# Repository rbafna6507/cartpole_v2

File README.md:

# Cartpole v2

Start here: [complete system README](SYSTEM_README.md), [command cheat sheet](COMMAND_CHEATSHEET.md), [all CLI arguments](COMMAND_REFERENCE.md), [source/evidence index](SYSTEM_REFERENCE.md), and [preservation audit](PRESERVATION_AUDIT_20261023.md).

October 26 offline developer update: [start with one controller in simulation, replay and submission](docs/CONTROLLER_DEVELOPER_GUIDE.md), use the [agent-facing portal API](docs/portal.md), and [export run bundles for analysis](docs/RUN_RECORDING.md). These source changes share the pinned `rig-calibrated-20261021-v1` development profile; deploying them and accepting full-duration physical runs remain separate work. Native/Python AUTO are hand-designed controllers, not separately trained policies; see the [offline comparison](docs/python-auto-offline-audit-20261026.md).

October 23 operator release: on the Jetson, `cd ~/cartpole-v2-live/active && uv run cartpole`, or use `cartpole-console` from PATH. In the console, load `policies/working.json` (user-tested 102,400 steps) or `policies/1m.json` (1,024,000-step candidate), then use `policy check swingup` and explicit `policy swingup 25` from a settled, homed hanging start. Deployment itself performs no motion.

For the vertical-enabled runtime, use the deployment copies `policies/working.json` and `policies/1m.json`. Their weights, experiment identities, and observation/action contracts are unchanged; only the reviewed runtime pins and enclosing content digest were migrated. [Migration evidence](policies/vertical-runtime-migration.json) records the original and deployed hashes plus exact numeric inference parity. Original `training/candidates/.../actor.json` files remain immutable and pinned to their archived runtime; the strict loader intentionally refuses them under changed runtime sources. This migration does not confer hardware acceptance.

Locally, `uv run --locked --extra sim cartpole-view-policy` opens the learned Gym viewer; add `--controller reference` for the saved traditional gains on the fitted plant, or `--actor policies/1m.json` for the new candidate. See the cheat sheet for all training, evaluation, console and deployment options.

The sections below retain earlier subsystem introductions. Dated historical measurements: [2026-10-20 checkpoint](docs/checkpoint-20261020.md).

The SDK now connects to a new Teensy safety executor, runs the preserved controller
on hardware, and supports Python policies, MuJoCo simulation, policy training,
recordings, source-specific sensing, and an isolated submission queue. The working
controller and vision3 remain unchanged in `archive/`.

The real SDK/Teensy path completed a ten-second swing-up/balance trial and a slow
return to center. USB telemetry delivered up to 1,000 Hz in stopped tests; a
250 Hz zero-command loop and action expiry were also verified. This does not
establish hard real-time host control or hardware acceptance of learned policies.

## Collect the remaining system identification data

Use `./scripts/system-id-campaign` for repeatable cart-response/timing/AUTO
campaigns and guided motor-disabled angular/cart measurements. Start with
`./scripts/system-id-campaign plan`; an offline `rehearse` command exercises the
artifact/review workflow without hardware. See [collection commands, review,
and portable evidence bundles](docs/system-id-campaign.md). Collection does not
change the existing simulation or trained policy profiles.

## Open the interactive demo

```bash
uv run --locked --extra sim cartpole-v2-view
```

Space pauses, R resets, and Esc exits. The command selects `mjpython` on macOS.
The initial overlay deadlock is fixed and native rendering/pause/reset have been
verified. Episodes intentionally freeze at 30 simulated seconds until R.
See [viewer controls and verification](docs/viewer.md).

## Use the new firmware and SDK

With the executor already installed, inspect the stopped board on the Jetson:

```bash
uv run --locked --extra hardware cartpole-console \
  --port /dev/serial/by-id/usb-Teensyduino_USB_Serial_20242870-if00 --command info
```

The console also provides `auto`, `bal`, external policies, homing, and explicit
switchless commissioning. Read [rig usage](docs/rig-usage.md) before motion and
[executor protocol and programming](docs/executor.md) before uploading firmware.
**Motor power must be off during every flash, bootloader entry, or board reset.**
The existing PCB does not hold the shared enable input disabled without firmware;
clicking was observed during programming and the board was recovered with motor
power off. A hardware default-disable circuit remains necessary.

[PCB switch wiring](docs/pcb-switches.md) specifies normally-closed contacts.
Switch 1 is the left cart limit and switch 2 the right. Physical two-end homing
measured 619.2 mm of travel; `rehome` returns to the established center. Only these
two switches are required for cart motion. Uninstalled D28/D29 remain diagnostic
inputs, Z pulses are disabled, and every boot enables the cart switch interlock.
See [current commands and commissioning evidence](docs/rig-usage.md).

The current operator release is `platform-20261015-v6-tunable`, running
`executor-v6-measuredrail`. The console loads the preserved bandwidth-10 gains
by default (`pw=3`, jerk 150 m/s³). Repeated native AUTO trials captured in about
2.5 seconds; two 60-second trials held continuously for about 57.5 seconds after
capture. A separate bandwidth-8 smoothing candidate also completed a 60-second
trial with return. These are measured bounded results, not unlimited stability.
The working encoder reference is 330 counts, an experimental constant trim;
there is still no accepted hanging-only or nonlinear calibration model.

See the [October 16 checkpoint](docs/checkpoint-20261016.md),
[tuning and jitter evidence](evidence/phase3/jitter-20261016/README.txt), and
[preserved Jetson releases](releases/README.md). The experimental Python AUTO/BAL implementation now runs through the SDK on the
physical rig. One 25-second Python AUTO trial captured at 3.17 seconds and held
for the remaining 21.8 seconds; other trials exposed host timing and an early
right-switch stop. It is not yet a repeatably commissioned replacement for native
control. See [Python control, gain explanations and identification](docs/python-control-20261016.md).
Release snapshots preserve the established native operator software separately.

## Persistent vision and SDK sensing

The maintained camera runtime is `src/cartpole_vision`; `archive/vision3` stays
unchanged. The Jetson's `cartpole-vision.service` keeps the camera portal running
independently of the console. From a computer on the same Tailscale network:

```sh
python3 scripts/vision-view.py --host 100.126.59.18 --port 13090
```

Open **http://127.0.0.1:13090/**. The portal provides camera, tracked overlay, green
mask, measured rates and plots. The v2 console automatically publishes its
accepted encoder telemetry; closing it marks encoder readings stale while the
camera continues. The camera service never opens serial. An isolated vision
environment prevents normal console installs from removing its dependencies.

[Vision setup and measured performance](docs/vision-usage.md) describes the private
viewer, SSH fallback, service and camera configuration. [SDK sensing](docs/sensing.md)
describes explicit frames and timestamps, the actual shadow fusion monitor, and
hanging model validation. Shadow fusion was verified against stopped live data;
it remains uncommissioned and does not control motion.

## Policies, identification and the portal

- [Host-rate Python control and reproducible RL](docs/policies.md): separate
  100/250 Hz controllers, raw-demand executor simulation, training and held-out
  evaluation. The learned artifact is numeric JSON; hardware transfer is unproven.
- [Model-bound PPO and Colab training](docs/rl-training.md): neural training,
  checkpoint resume, disjoint evaluation and a portable SDK actor using the
  governed/observed simulator. Current model scopes remain development only;
  physical model and learned-policy acceptance are separate gates.
- [Sensing and physical identification](docs/identification.md): explicit clocks,
  calibration, validity and held-out rejection. The MuJoCo plant remains provisional.
- [Runnable system-identification workflow](docs/system-identification-workflow.md):
  labelled release protocols, raw-data and frozen-fit plots, independent validation,
  scoped model export and Gym loading. [PPO and Colab](docs/rl-training.md) adds
  neural training, resumable checkpoints and a portable SDK actor using the
  governed, encoder-observed `RigCartpoleEnv`. Physical-model acceptance remains
  separate from software readiness.
  [October 17 measurements and plots](evidence/system-id-20261017/README.md) record
  the latest physical results; model acceptance for hardware RL remains open.
- [Portal and isolated worker](docs/portal.md): authenticated immutable uploads,
  durable single-rig queue, results and a Linux sandbox. The service defaults to
  loopback. Public hosting and learned-policy hardware acceptance remain deployment gates.
- [Current implementation and acceptance state](docs/platform-status.md).
- [Detailed execution plan](docs/live-rig-plan.md).

## Try the controller in simulation

```bash
mkdir -p runs/demo
uv run --locked --extra sim cartpole-v2 simulate runs/demo/swingup --steps 10000
uv run --locked --extra sim cartpole-v2 simulate runs/demo/upright --start upright --steps 10000
uv run --locked --extra sim python examples/gym_rollout.py --steps 200 --seed 7
```

The first two commands save observations, action/plant traces, model and parameters
in new directories. The model uses provisional physical parameters; successful
simulation does not establish hardware transfer. See [Phase 2 usage](docs/phase2-usage.md)
for custom Python policies, Gymnasium, sensor timing, model configuration and limits.

## Try the Python SDK locally

```bash
mkdir -p runs/sdk-demo
uv run --locked cartpole-v2 import-vision tests/fixtures/vision-real.jsonl runs/sdk-demo/vision.jsonl --session-id demo-vision --frame-id vision:demo-calibration
uv run --locked cartpole-v2 inspect runs/sdk-demo/vision.jsonl
uv run --locked python examples/replay_policy.py runs/sdk-demo/vision.jsonl runs/sdk-demo/my-policy.jsonl --frame-id vision:demo-calibration
```

Edit `MyPolicy` in `examples/replay_policy.py` to experiment. The example receives
real recorded vision observations and writes acceleration requests to a local
trace. Replay uses fixed inputs; it does not simulate the resulting rig motion.
The example is an illustrative mapping, not the tuned balancing controller.
Outputs are never overwritten; choose fresh paths when repeating commands.

See [SDK usage, data semantics and next integrations](docs/phase1-usage.md).
Run maintained tests with
`uv run --locked --extra sim --extra hardware --extra vision --group dev python -m pytest`
(C++17 compiler required for native firmware tests). Archived projects retain
their own separate environments and test commands.

## Run the baseline

The archived console requires the original v33 firmware. The currently installed
executor uses the new console above; the two wire protocols are different. Restore
an archived firmware only with motor power off. With v33 installed, run from the
repository root on the Jetson:

```bash
uv run --project archive/good_balancing_jetson cartpole-console --rate 100
```

The console restores the saved tuning while stopped, verifies 33 parameters and
8 computed gains, and opens the terminal interface. It does not start motion or
restore an old home/upright reference. Close any other Teensy console first.

To use the preserved camera baseline instead of the maintained service, first stop
`cartpole-vision.service`, then run in a separate Jetson terminal with no other
camera owner:

```bash
cd archive/vision3
uv run vision3 --camera /dev/video0 --calibration-file last_calibration.json
```

On the Mac, from the repository root:

```bash
./archive/vision-tunnel.sh
```

After SSH connects, open **http://127.0.0.1:3095/**. Keep the tunnel terminal open.
The tunnel discovers the current direct IPv6 address through a read-only query
using `ssh rbafna@jetson`, then verifies reachability and reuses the trusted host identity.
It needs a working bootstrap SSH key/agent; the final connection can still ask for
your normal password. To preview the selection, use
`./archive/vision-tunnel.sh --print-command`. An explicit destination bypasses
discovery: `./archive/vision-tunnel.sh rbafna@jetson` uses the configured route.
It does not start the camera or control the rig.

- [Jetson setup and testing](docs/jetson-testing.md)
- [Archive contents and recovery](archive/README.md)
- [Console, gains, and firmware](archive/good_balancing_jetson/README.md)
- [Vision, calibration, and system dependencies](archive/vision3/README.md)
- [Control rates, languages, and transport choice](docs/control-timing-and-transport.md)
- [Revised v2 architecture](docs/architecture.md)
- [Phase 2 implementation plan](docs/phase2-plan.md)
- [Phase 2 verification](evidence/phase2/verification.json)
- [Phase 1 implementation plan](docs/phase1-plan.md)
- [Phase 0 plan and decisions](docs/phase0-plan.md)
- [Phase 1 verification](evidence/phase1/verification.json)
- [Phase 0 verification](evidence/phase0/verification.json)

Both projects pin Python 3.11 for `uv` and include a universal `uv.lock`. Their
commands are intended to run from an editable repository checkout; this archive
is not a standalone wheel distribution. Do not copy `.venv` between computers.

No Jetson access, camera capture, firmware upload, or physical motion was performed
during Phase 0. New control and vision work uses directories outside the preserved archived
baselines; later physical work is recorded under `evidence/phase3` and `phase4`.

Controller authors: [SDK data and development guide](docs/CONTROLLER_DEVELOPER_GUIDE.md). The portal now requires operator approval for each physical job; the deployed worker, expanded upload formats and Vercel migration are documented in [Portal deployment](docs/PORTAL_DEPLOYMENT.md).

### Vertical screw commissioning

The separate [vertical actuator test](docs/VERTICAL_COMMISSIONING.md) documents
D4/D5 and D6/D7 wiring, independent direction checks, operator-declared bottom
reference, timed bottoming and bounded paired sine motion. It requires a temporary
standalone Teensy firmware and cannot run concurrently with pendulum controllers.
This earlier standalone commissioning path remains available for isolated checks.
The integrated `cartpole-console` implementation is described below.

### Integrated vertical controls

The [integrated vertical guide](docs/VERTICAL_CONTROL.md) covers the
`executor-v7-vertical` firmware and `z` commands in the normal console: independent
or paired physical up/down moves, timed bottoming, explicit bottom reference,
vertical STOP and finite paired disturbances. The staged height-limit build defaults
to a firmware-enforced 120 mm ceiling; `z limit [MM]` reads/sets it (10..200 mm)
while stopped. Reflash instructions are in the integrated guide. Left UP is DIR LOW; right UP is
DIR HIGH. Hardware commissioning status and staged-release instructions are in
the guide; the standalone test remains available separately.

### Policy requirements and camera recording

Learned policies own their action decisions; native swing-up/balance gains no
longer need to match their archived training snapshot. Observation filtering and
shared hardware motion/safety requirements still apply. See
[policy executor requirements](docs/policy-executor-requirements.md).

Camera recording is bounded and storage failures are reported without stopping
tracking or video. See [camera recording](docs/camera-recording.md). Portal jobs
use the same Jetson API, SQLite queue, and filesystem artifacts whether the
frontend is served through Funnel or Vercel; see
[portal deployment](docs/PORTAL_DEPLOYMENT.md).

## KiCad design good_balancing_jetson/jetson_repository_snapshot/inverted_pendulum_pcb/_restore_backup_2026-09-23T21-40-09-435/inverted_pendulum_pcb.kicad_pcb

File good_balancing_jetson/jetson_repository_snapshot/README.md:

# Cart-pole: ESP32 firmware + Mac host console

## Manual cart frequency test

Use the [frequency-test GUI](frequency_test/README.md) to choose peak-to-peak
travel and frequency, preview position/velocity/acceleration/jerk, and run the
cart manually. It uses a separate ESP32 test sketch. Swing-up auto-tuning is
paused during these tests.

## Run the swing-up sketch (125 mm arm, 60T pulley, 300 mm travel)

**v34:** startup now uses the [full-span hardware tuning preset](analysis/v33_span_tuning/recommended_settings.json):
`ke=4`, `kpx=40`, `kdx=2`, `pw=6`, `pz=0.85`, `pc1=-3`, `pc2=-4`,
`bw=30`, `catch_a=0.25`, `catch_r=2`, and `catch_da=2`.
Motion defaults are `vmax=vmax_s=vmax_b=1.5`, `amax_s=amax_b=25`,
`jmax=150`, and `spin_trip_rad_s=150`. Normal operating travel remains 270 mm.
This preset achieved three 30-second holds, with variable capture latency;
it is the supported full-span preset, not the experimental compact-span candidates.
Manual upright mode retains `bal_pw=8` and uses the shared cart poles.
`bw` remains adjustable from 0.1–100 Hz while stopped.
Upload v34 manually to apply these defaults; this source update does not flash the board.

v32 added a bounded startup kick from centered hanging rest, subject to the same
jerk and rail protection. Physical tuning results and per-trial settings are in
`/Users/sajivshah/Documents/InvertedPendulum/autonomous_tuning/20260918_resume/`.
The 60T pulley, 125 mm arm, and cart STEP25/DIR26 mapping are retained. `params`
should report `pulley_teeth 60`, `cart_mm_per_rev 120`, and `cart_steps_per_m 26666.67`.

`swingup/swingup.ino` runs on the ESP32; `cartpole.py` is its Mac console.
The swing-up cart pins are **STEP = GPIO25, DIR = GPIO26**.
Z1 uses **STEP = GPIO18, DIR = GPIO19**; Z2 uses **STEP = GPIO16 (RX2), DIR = GPIO17 (TX2)**.
The older sketches below retain their own wiring.
Place the cart at the **physical center** before power-up/reset. Support the
pendulum as needed. Startup loads the saved upright reference and assigns `x = 0` there;
there is **no homing movement**. The sketch boots idle with **all drivers disabled** and these cart limits:

| Setting | Default |
|---|---:|
| Total physical travel | 300 mm (±150 mm from startup center) |
| Hard speed ceiling (`vmax`) | 1.5 m/s (750 RPM) |
| Swing / balance operating caps (`vmax_s` / `vmax_b`) | 1.5 / 1.5 m/s |
| Near-upright approach speed / capture speed (`approach_v` / `catch_v`) | 0.3 / 0.3 m/s |
| Swing-up acceleration limit (`amax_s`) | 25 m/s² (12,500 RPM/s) |
| Balance/braking acceleration limit (`amax_b`) | 25 m/s² (12,500 RPM/s) |
| Manual acceleration limit (`amax_m`) | 0.5 m/s² |
| Automatic jerk limit (`jmax`) | 150 m/s³ (75,000 RPM/s²) |
| Manual jerk limit (`jmax_m`) | 10 m/s³ |
| Keyboard jog speed (`vman`) | 0.05 m/s |

The 60T pulley and 2 mm belt pitch give 120 mm/revolution and 26.666667 steps/mm
at 1/16 microstepping. At `jmax 150`, acceleration changes by at most
0.15 m/s² per 1 ms tick, taking approximately 167 ms from zero to 25 m/s².
A 7 µs pulse timer supports up to 71,429 steps/s (2.679 m/s pulse ceiling);
the configured 1.5 m/s limit requires 40,000 steps/s.
Manual jogging keeps its gentler acceleration and jerk limits.
`stop`, `off`, and faults stop pulses and **disable all three drivers**.
Startup drives the shared active-low ENABLE pin HIGH before serial delays,
I2C initialization or encoder zeroing. Support the height assembly while
motors are disabled. Firmware cannot control GPIO during the earlier reset/bootloader interval.
There are no `fast` or `slow` profiles; motion commands use the current limits.

### v26: prepare for capture, independently of the hard speed ceiling

`vmax_s` and `vmax_b` independently cap swing-up and balance; both are bounded by
`vmax`. Raising an unused hard ceiling does not change pumping or capture.
Both operating caps start at 1.5 m/s: reducing the entire swing phase prevented
energy buildup in many modeled cases. The approach to upright has its own slower policy.

On the incoming arc, `approach_angle=0.8` rad (46°) begins blending the energy
pump into balance feedback and reducing planned speed toward `approach_v=0.3` m/s.
Capture additionally requires speed below `catch_v=0.3` m/s, balance demand within
`catch_da=2` m/s² of the current acceleration, and a feasible 180 ms forecast.
The forecast checks jerk, speed, rail braking and angular divergence. It is a
model-based gate, not a guarantee of motor tracking. Acceleration always passes
through the shared jerk limiter, including handoff and return to a lower mode cap.

Changes require `stop` first. For example, `set vmax_s 0.8`, `set vmax_b 0.8`,
`set approach_v 0.3`, and `set catch_v 0.3`. The v26 trial used
`ke=8`, `kpx=80`, `kdx=2`, `phase_soft=2`, `pw=7`, `pz=0.85`;
v34 startup gains are listed above.
[Evidence, validation and remaining limitations](analysis/v26/README.md).
**v26 uploaded; firmware, defaults, IDLE and disabled output verified over serial. No physical motion trial yet.**

### User-set motion ceilings (v34)

Firmware enforces maximums of `spin_trip_rad_s 150`, `jmax 150`,
`amax_s 25`, `amax_b 25`, and `vmax`, `vmax_s`, `vmax_b` all 1.5.
Boot defaults match these. `bw` defaults to 30 Hz and is independently
tunable. The trial runner reapplies and verifies its recorded settings before motion.
Lower values remain manually configurable while stopped.

Trials require a usable encoder magnet, a known cart origin, and supervision.
Keep one serial connection open between trials: opening this board's port resets
its pulse-based position origin. Re-establish the origin after a reset; `home`
sets the current position to zero and does not physically seek the center.
Cart position is inferred from pulses and cannot detect all missed steps.

### Adjustable spin recovery (introduced in v29)

**Uploaded and serial-verified: trigger 50 rad/s, resume below 10 rad/s, bw 30 Hz; IDLE with drivers disabled.**

```text
stop
set spin_trip_rad_s 50
set spin_resume_rad_s 10
params
```

v29 defaults were 50 rad/s to trigger recovery and below 10 rad/s to resume once centered and stopped. Both values use the magnitude of filtered pendulum rate. Changes require IDLE and `0 < spin_resume_rad_s < spin_trip_rad_s`. Runtime changes last until reset; v30 startup defaults are 150/10. Messages and `get`/`params` report the active values. Manual `bal` retains its separate fall-and-return behavior.

### Encoder rate filtering (v28, included in v29)

The default `bw` is now **30 Hz**, up from 10 Hz. The same wrap-aware observer
still updates at 1 kHz. Quantized-sine tests at 1–5 Hz show rate-estimate phase
delay falling from 28–30 ms to about **9 ms**. This is filter delay only, not
measured end-to-end motor response. Higher bandwidth increases rate noise.
The 25 Hz telemetry logs cannot validate millisecond-scale sensor noise.

```text
stop
set bw 30
params
```

v28 accepts `bw` only in **0.1–100 Hz**, while stopped, and resets the estimator
state in the control task after a bandwidth change. v27 accepted `bw 500`, which
made the estimator diverge in the September 18 12:33 recording; that setting
must not be used. If an older board has already diverged, stop and reboot it to
clear the state before applying a valid bandwidth. Re-establish physical cart
center before a reset because startup assigns x=0 without homing.

Firmware and simulator defaults both use 30 Hz. Saved historical presets retain
their recorded bandwidth. Gains, motion limits, encoder reference, and pins are
unchanged by this revision. This change is compiled and tested offline; hardware
balance performance remains unverified.

### Quick upright calibration (v27)

**v27 uploaded and serial-verified.** With the arm physically vertical, use:

```text
stop
upright
```

Keep it still until `encoder reference saved` appears (about 0.4 s of steady
readings, with a 5 s timeout). This records the present encoder count as
`theta=0` for balance, capture and telemetry, and resets the estimator.
It does not enable the motors. After the saved acknowledgment, `stat` should
show an angle close to zero. If the cart is physically centered, `home` then
`bal` starts an upright-only trial.

- `upright` averages a still vertical reading, handling the raw count wrap.
- `upright 3769` sets a known count directly; **3769 is only an example**.
  Counts must be integers from 0 through 4095.
- `zero` is for the arm **hanging down**. It records down and updates the
  upright target by half a turn (2048 counts), with the same stillness check.
  Do not use `zero` while the arm is upright; use `upright` instead.
- `home` resets cart position only.

Both reference commands stop and disable every motor. Support the height
assembly. Motion is blocked during capture and saving; `stop` cancels an
unfinished capture. Invalid encoder readings cannot complete calibration.
The saved target survives reset and startup does not overwrite it from the
arm's boot position. A board without a saved reference falls back to the old
3953 count calibration until you explicitly use `upright` or `zero`.
`params` reports the live `encoder_upright_raw` and `encoder_reference_saved`.
If saving fails, the acknowledgment says the reference is active only until reset.

`bal` rejection now reports the measured/estimated angles, angular speed and
cart position to identify a failed start condition. Uniform 4096-count scaling
remains; these commands change the offset, not encoder nonlinearity.
The [original four-pose readings](encoder_calibration/125mm_20260917/selected_calibration.json)
remain an unchanged historical record.

### Pendulum spin failsafe

**v24 trips immediately above |θ̇| = 35 rad/s and releases below 10 rad/s. Reflash to apply it.**
`params` reports `spin_trip_rad_s 35` and `spin_resume_rad_s 10`.

The filtered angular-speed magnitude **above 35 rad/s** latches
`SPIN_BRAKE → SPIN_CENTER → SPIN_WAIT` in either rotation direction.
It monitors automatic swing-up, automatic balance, and automatic rail recovery.
The upright-only `bal` trial retains its separate fall-return-stop behavior.
There is no full-turn requirement, pendulum-angle gate, or quiet-time delay.

Pendulum control pauses while the cart brakes, then returns to its original
center at up to **0.10 m/s**, with a **0.5 m/s²** return acceleration target and
the existing jerk limit. Braking still uses the normal motion/rail protections.
SWINGUP resumes only once the cart is within **±3 mm** of center,
|cart velocity| ≤ 0.005 m/s, |cart acceleration| ≤ 0.1 m/s², and a valid
encoder estimate has **|θ̇| strictly below 10 rad/s**. Exactly 10 rad/s keeps
waiting. The separate thresholds prevent repeated switching near the trip rate.
Waiting can continue indefinitely; failure to center within 10 seconds faults
and disables the motors. Ordinary edge recovery still only returns inside the
270 mm operating region; this rate failsafe specifically returns to center.

Drivers remain enabled to hold center during recovery. `stop`/`off` cancel it
and disable all drivers immediately. Repeated `auto`, `bal`, and jog commands
cannot bypass an active recovery. `stat` shows its phase, current rate, and
release threshold.
There is no homing or direct cart-position measurement; the center reference
still relies on commanded steps and can be wrong after physical slipping.

### Rail recovery

The physical ends are at ±150 mm from the startup center. Normal operation may
use the central **270 mm (±135 mm)**. Entering the last 15 mm at either end
starts `RAIL_BRAKE`: pendulum control pauses while outward motion decelerates.
Predictive braking can start earlier when velocity and acceleration require it;
it aims to stop before ±135 mm. At 0.8 m/s with zero acceleration and jerk
60 m/s³, stopping requires about **92.4 mm**, so braking cannot wait for the
last 15 mm at full speed.

Braking now finishes with both speed ≤0.005 m/s and acceleration ≤0.1 m/s²
before `RAIL_RETURN` requests an inward speed up to 0.15 m/s and
acceleration up to 1.5 m/s² (or lower configured limits), still jerk limited.
The stopping prediction includes the final ramp of acceleration back to zero.
Automatic operation resumes SWINGUP inside **±130 mm**, moving inward or
nearly stopped with inward acceleration, only once |speed| ≤0.155 m/s,
|acceleration| ≤1.5 m/s² and the braking latch has cleared. This prevents
handing swing-up a fast, strongly accelerating return from the rail.
There is no center-seeking or dwell. Recovery can finish farther inside if the
predictive stop completed there. A `# rail handoff` event records x, v and a.
[Recovery checks and compact swing-up tuning](analysis/rail_recovery_v22.md).
Manual recovery resumes MANUAL with a zero velocity target. Held jog commands
are ignored during recovery; `stop` always cancels recovery and disables all
drivers. Recovery never resets the position reference. It times out to a
disabled fault after 8 s.

The independent fault boundary remains ±140 mm. Position is inferred from
commanded steps, not sensed at the ends; missed steps or manual movement can
invalidate it. These are software margins, not physical endstop detection.

Close other serial programs before uploading. Reset/upload releases the shared
driver enable, so support the height assembly. From Terminal:

```bash
cd /Users/sajivshah/Documents/GitHub/cartpole_inverted_pendulum
python3 flash.py swingup
python3 cartpole.py --port /dev/cu.usbserial-0001
```

### Compile and flash any sketch

`flash.py` requires Python 3, `arduino-cli`, and the installed board core (see
setup below). It defaults to `swingup` and the `esp32:esp32:esp32` board. It
selects the single connected USB serial device; with multiple devices, specify
`--port`. Close the serial console or plotter first.

```bash
python3 flash.py                          # compile + flash swingup
python3 flash.py frequency_test           # any sketch in this repo
python3 flash.py characterize/characterize.ino
python3 flash.py swingup --port /dev/cu.usbserial-0001
python3 flash.py swingup --compile-only   # compile without accessing hardware
python3 flash.py /path/to/sketch --fqbn vendor:architecture:board --port PORT
```

You can invoke the script by its full path from any directory. Sketch names
resolve from the current directory first, then from this repo. Paths containing
spaces must be quoted. Use `--libraries DIR` for extra libraries or `--cli PATH`
for an Arduino CLI installation outside your PATH. The bundled FastAccelStepper
library is included automatically. `python3 flash.py --help` lists all options.

Every invocation builds in a fresh temporary directory and uploads that exact
build only if compilation succeeds. Temporary files are removed afterward.
The script does not open a serial monitor or send motion commands; the selected
firmware determines startup behavior after upload.

If Python dependencies are missing, install `pyserial` and `matplotlib` in your
Python environment. The port may change after reconnecting; check `/dev/cu.*`.
The [Arduino CLI guide](https://docs.arduino.cc/arduino-cli/getting-started)
describes the compile/upload commands.

Wait for `# ready`, then at the `>>>` prompt:

```text
params
mag
auto
```

`auto` enables the drivers, starts swing-up and switches to balance when eligible.
`stat` reports the ENABLE output: LOW means enabled, HIGH means disabled.
v9 fixes v8 GPIO initialization that could report energized while ENABLE stayed HIGH.
While plotting, type **`stop` + Enter in the terminal**, click **STOP / disable**,
or press **Space/Escape in the plot**. In the terminal, Escape or Space at an
empty prompt also sends stop immediately. `q` + Enter exits the plot and stops.
Other terminal commands, including `set`, work while plotting. A/D/W/S jogging
is available in the `control` plot window; terminal letters form commands.
Restart `cartpole.py` to load this console change. Reflash v15 for the serial fixes, calibrated upright, rail
behavior and limits. No profile command is needed.
After moving the disabled cart by hand, place it at physical center and issue
`home` before starting again; commanded steps cannot observe manual movement.
Height-axis limits remain 2 mm/s and 20 mm/s².

To change limits, first send `stop`, then for example:

```text
set vmax 0.8
set vmax_s 0.8
set vmax_b 0.8
set approach_v 0.3
set catch_v 0.3
set amax_s 12
set amax_b 12
set jmax 60
set rail 0.15
```

`rail` is **half** the total physical travel, in metres. These serial settings
last until reset. `home` only
relabels the stopped cart's current position as zero; use it only at the physical
center. It does not search for a limit switch.

Both JSON files record 300 mm total travel. The current arm is **125 mm / 11.05 g**
with **two 5.85 g end weights**, 22.75 g combined. The original 100 mm label
was incorrect; the user confirmed it referred to this same 125 mm arm.
JSON is reference metadata, not automatically loaded by the sketch.
The current controller uses **0.124 m effective length**, rounded from
**0.124455 m**, fitted from 20 same-side cycles at 5–20° across three of the
original pre-175 mm captures. Period is 0.707704 s; simulator equivalent
viscous damping is 0.913383 s⁻¹. Balance gains, energy normalization and
capture prediction all use the updated length. The pole choices and motion
limits remain unchanged. [125 mm fit and source records](pendulum_characterization/125mm_11p05g/2026-09-15/README.md).
The live encoder upright target is saved on the ESP32. Use `upright` after
re-indexing the shaft or encoder magnet.

The revised `swingup-175mm-20t-v15` firmware uses smooth phase feedback for energy
pumping, cart centering, a gentle startup bias, and a balance handoff that also
checks cart position, speed headroom, approach direction, and acceleration ramp time.
The capture window opens at 0.60 rad (34.4°), with angular rate below 3 rad/s;
balance acceleration applies on the handoff tick. The dropout angle is 0.80 rad.
The speed limiter anticipates velocity gained during acceleration ramp-down. It stops startup if it
commands over 30 mm cumulative travel for over 2 seconds without a 0.03 rad
pendulum response. This detects gross non-response; it does **not** detect every
missed step. Buzzing with little physical movement still needs a motor/driver
check and a fresh physical center reference. Verify manual motion first. Motion-limit regressions pass for this revision, but
recorded-state simulations remain imperfect: some cases settle in the ideal
model despite failing physically. See [current change assessment](analysis/rail_recovery_v10.md) and the earlier [v8 assessment](analysis/v8_assessment.md).

The console now saves `logs/run_<timestamp>_events.jsonl` alongside each CSV.
It records outgoing commands, firmware identity, parameter replies, diagnostic
messages and faults; `auto` and `bal` request a parameter snapshot before starting.
Cart position is inferred from pulses, and velocity/acceleration are commands.

### Ongoing log review

The five-minute Codex review is currently **paused for manual frequency tests**.
When enabled, it reviews new completed runs and updates
and tests repository candidates; applying settings and starting trials remain
manual. The controller does not learn online. See [tuning workflow and current
candidate](analysis/continuous_tuning.md). Keep Codex open and this Mac awake.

Host-side motion regression checks (no hardware movement):

```bash
clang++ -std=c++11 -Wall -Wextra -Werror tests/cart_motion_test.cpp -o /tmp/cart_motion_test
/tmp/cart_motion_test
clang++ -std=c++11 -O2 -Wall -Wextra -Werror tests/swing_controller_test.cpp -o /tmp/swing_controller_test
/tmp/swing_controller_test
python3 tests/test_console_events.py
```

## Free-swing recording: automatic stop

Recorded datasets are indexed in [pendulum_characterization/README.md](pendulum_characterization/README.md), grouped by physical configuration and date.

The `characterize` sketch ends with `END quiet` when the encoder stays within
**1° peak-to-peak for 3 seconds**, after at least 7 seconds of recording. It uses
unwrapped angle counts, so one-count encoder noise does not restart the quiet
timer. Motion above that band restarts the timer; missing samples or sensor
errors also restart it. The 45-second maximum capture remains a fallback.

Recompile and upload `characterize` to apply this change, then rerun the host:

```bash
arduino-cli compile --fqbn esp32:esp32:esp32 characterize
arduino-cli upload --fqbn esp32:esp32:esp32 -p /dev/cu.usbserial-0001 characterize
python3 characterize_pendulum.py --port /dev/cu.usbserial-0001
```

Close other serial consoles, support the height assembly, and keep the cart
fixed with motors off for the free-swing test. Start hanging, displace the
pendulum about 10–20°, and release. The Python recorder also sends `STOP` when
its own timeout expires or you press Ctrl-C.

Replay the two recordings that previously reached the 45-second timeout:

```bash
clang++ -std=c++11 -Wall -Wextra -Werror tests/quiet_motion_test.cpp -o /tmp/quiet_motion_test
/tmp/quiet_motion_test pendulum_characterization/175mm_14p2g/2026-09-15/pendulum_20260915_184743.csv pendulum_characterization/175mm_14p2g/2026-09-15/pendulum_20260915_184905.csv
```

With the new detector, those captures qualify as quiet at approximately
19.1 seconds and 25.1 seconds respectively. This is an offline replay, not a
new hardware measurement.

## Serial integrity and encoder recording (v15)

**Flash v15 and restart the updated console together.** They use **115200 baud**
and **25 Hz telemetry** (maximum 100 Hz). Replies carry a CRC-16 checksum,
including telemetry, raw encoder readings, parameters and STOP acknowledgments.
Dropped digits and minus signs are rejected even when the remaining text looks
like a valid number. Host commands remain newline-delimited text.

The console sends keepalives every 250 ms without depending on parameter replies.
Firmware disables active motion after 1.5 seconds without host commands. The
console sends STOP after a one-second telemetry gap, retries STOP/rate commands
once per second as needed, and requires a valid STOP acknowledgment and three
consecutive valid telemetry samples before permitting a new motion command.
It never replays a previous run. Startup follows the same STOP acknowledgment
check. A blocked `auto`/`bal` stays at the prompt instead of opening a dashboard.

Type **`link`** in the terminal (also while plotting) for the exact blocking
reason, valid sample rate, and checked/rejected frame counts. Malformed frames
and blocked requests are logged. Automatic recovery retries the same serial
path; a different port name needs a console restart with the new `--port`.
Check physical cart center after a USB reconnect/reset before restarting motion.

The 14:06–14:09 sessions show dropped characters, stale telemetry and one
`Device not configured` disconnect. Lower baud/traffic and chunked host reads
reduce serial load; checksums detect corruption rather than reconstruct missing
bytes. Physical USB reliability still requires a run on the hardware. See
[serial investigation](analysis/serial_integrity_v15.md).

For explicit diagnostics with old firmware only, the console accepts
`--legacy-serial --baud 230400` for v13/v14 (`921600` for older swing-up versions).
Unchecked legacy data cannot reliably detect dropped digits. The calibration
recorder now requires v15 checksummed replies, preserving the original captured
files. The live balance target is set by `upright` or `zero` in v27.

After flashing v15, close the console and run:

```bash
python3 calibrate_encoder.py --port /dev/cu.usbserial-0001
```

Hold the pendulum manually at each prompt and press Enter:

1. **0°** — hanging down.
2. **90°** — horizontal toward positive cart travel.
3. **180°** — upright.
4. **270°** — horizontal toward negative cart travel.

All motor drivers remain disabled. Each Enter records **one raw encoder reading**
and immediately saves it under `encoder_calibration/`. The JSON contains the
four reference angles and their raw counts, plus the original readings and
sensor diagnostic flags. Use `--samples 20` only if you want multiple readings
and a circular mean at each position.

The recorder does not reject motion, magnet flags, offsets, or quadrant spacing.
Unreadable serial replies are retried five times, then the same position prompt
remains available to retry. Earlier readings remain saved. These values form the
recorded calibration table; firmware correction is not automatically applied by the recorder. The current
v27 firmware can apply a recorded upright count with `upright <count>` as described above.
This serial update requires v15 firmware; older replies are rejected by default.

## Original cartpole_esp32 sketch

The remaining instructions describe the separate `cartpole_esp32` sketch,
including its older wiring and slow boot defaults. Its pulley conversion is also
60T; its linear limits are preserved. For the current 60T / 300 mm setup,
use the `swingup` commands above.

```
cartpole_esp32/cartpole_esp32.ino   flash this
cartpole.py                         run this
```

---

## 1. Wiring

Every STEP pin is deliberately in GPIO 0–31, because the firmware pulses all
three axes with a single register write. Don't relocate them above GPIO 31.

| ESP32 | Connects to | Notes |
|---|---|---|
| GPIO 25 | Cart driver — STEP | |
| GPIO 26 | Cart driver — DIR | |
| GPIO 16 | Z-left driver — STEP | |
| GPIO 17 | Z-left driver — DIR | |
| GPIO 18 | Z-right driver — STEP | |
| GPIO 19 | Z-right driver — DIR | |
| GPIO 27 | **ENABLE — all three drivers** | active LOW, wired in parallel |
| GPIO 21 | AS5600 SDA | |
| GPIO 22 | AS5600 SCL | |
| 3V3 | AS5600 VCC | module is a 3.3V part |
| GND | AS5600 GND **and its DIR pin** | DIR must not float |

Leave MS1/MS2/MS3 unconnected on **all three** drivers. The Big Easy Driver
pulls them high for its 1/16 default: 26.667 steps/mm on a 60T GT2 belt, 640
steps/mm on a 5 mm ball-screw lead.

The legacy sketch uses a 120 kHz configured timer and a 60T pulley. Its
configured fast profile remains 0.72 m/s and slow profile remains 0.05 m/s.
Use the swing-up sketch above for the current controller and safety settings.

All driver grounds tie to ESP32 ground. Motor power (24V) goes to **M+ only** —
the BED's VCC pin is a regulator *output*, not an input.

### Three things to do to the hardware first

**Solder the 3/5V jumper closed on all three Big Easy Drivers.** The A4988
needs V_IH ≥ 0.7×VDD, which is 3.5V when the board's logic rail is at its
default 5V. Your ESP32 drives 3.3V. It will half-work and drop steps
unpredictably, which is indistinguishable from a tuning problem.

**Set the current.** The BED uses 0.11 Ω sense resistors, so
`I = Vref / (8 × 0.11) = Vref / 0.88`. The ball-screw motors are 1.5A →
Vref = 1.32 V, measured at TP1 with the motor unplugged.

**Mind the air gap on the encoder magnet.** Aim for 1–2 mm, magnet rotation
axis exactly on the pivot axis. A 0.5 mm offset becomes a once-per-revolution
angle error the balancer will chase forever. The `mag` command reports AGC;
mid-range (~64) is good, railed at either end means bad gap or wrong magnet.

---

## 2. Flashing from a Mac, no Arduino IDE

```bash
brew install arduino-cli

arduino-cli config init
arduino-cli config add board_manager.additional_urls \
  https://espressif.github.io/arduino-esp32/package_esp32_index.json
arduino-cli core update-index
arduino-cli core install esp32:esp32
```

Find the board. The sketch folder name has to match the `.ino` name, which it
already does:

```bash
ls /dev/cu.*          # look for cu.usbserial-* / cu.wchusbserial-* / cu.SLAB_USBtoUART
```

Nothing there? You need the USB-UART driver for your dev board's bridge chip —
Silicon Labs CP210x or WCH CH34x, depending on which one it has. Check the chip
next to the USB connector.

Compile and upload:

```bash
arduino-cli compile --fqbn esp32:esp32:esp32 cartpole_esp32
arduino-cli upload  --fqbn esp32:esp32:esp32 -p /dev/cu.usbserial-0001 cartpole_esp32
```

If upload fails to sync, hold **BOOT** on the dev board, tap **EN**, release
BOOT, and rerun. Some boards need this every time; most auto-reset fine.

Watch boot output directly if you want:

```bash
arduino-cli monitor -p /dev/cu.usbserial-0001 --config baudrate=921600
```

---

## 3. Host console

```bash
pip3 install pyserial matplotlib
python3 cartpole.py
```

It finds the port itself. At the prompt:

| Command | What it does |
|---|---|
| `data` | live dashboard — angle, angular rate, cart position + velocity, commanded acceleration, pendulum energy, plus AGC / loop time / stream rate |
| `control` | **A** / **D** drive the cart left and right, **W** / **S** raise and lower the rail, **SPACE** stops, **Q** returns to the prompt |
| `auto` | swing-up, hands off to the balancer, dashboard open the whole time |
| `bal` | balance only — hold the pole upright and send this |
| `stop` | emergency stop |
| `slow` | crawl speeds — **the boot default** |
| `fast` | full speeds, needed for `bal` and `auto` |

Spacebar is a stop from inside any window, and it works whether the plot or the
terminal has focus. Ctrl-C at the prompt stops the board on the way out.

Every sample is written to `logs/run_<timestamp>.csv` automatically. `rate 250`
gives you a denser capture if you want to analyze a specific fall.

### Encoder angle crossings

The live angle plot keeps `0 = upright` and breaks its line at the ±π display
boundary. This avoids false vertical jumps when the arm swings past hanging
down. Telemetry and controller calculations are unchanged. Restart `cartpole.py`
to load the plotting fix; no firmware flash is required.

For a continuous angle plot and wrap-corrected angular-rate check from a saved
run (with its matching `_events.jsonl` sidecar):

```bash
python3 analysis/plot_encoder_run.py logs/run_<timestamp>.csv --output analysis/encoder_run
```

The report freezes the input files and saves PNG/SVG plots plus `summary.json`.
Unwrapping assumes less than half a rotation between samples and disconnects
gaps longer than 0.2 seconds. It does not correct sensor nonlinearity.

### How the keyboard driving is safe

Holding **A** doesn't latch a velocity. Each key repeat sends a fresh `v`
command, and the firmware zeroes the cart if it hasn't heard one in 250 ms. If
the host crashes, the USB cable pops out, or you just let go, the cart stops on
its own rather than driving into the end of the rail.

### Emergency stop keeps the motors energized

`stop` zeroes every velocity but leaves the drivers on. That's deliberate: the
SFU1605 screws are efficient enough to back-drive, so cutting ENABLE with the
rail raised drops it. Since all three ENABLE lines share GPIO 27, de-energizing
is a separate command — `off` — and you should support the rail before using it.

---

### Speed profiles

The board boots into `slow`: 0.05 m/s top speed, 0.02 m/s jog, 1 m/s² accel.
Everything creeps, and a direction error nudges the end of the rail instead of
hitting it. Do all of your wiring and calibration checks here.

Balancing will not work on the slow profile, and that isn't a tuning problem —
the cart has to accelerate out from under a falling pole, and 1 m/s² isn't
close. Send `fast` before `bal` or `auto`, and stand clear when you do.

Both commands e-stop first, so `slow` doubles as a panic button that also
prevents the next command from being quick.

## 4. First run, in order

1. **Current down, motors nowhere near the rail ends.** `python3 cartpole.py`,
   then `mag` — confirm the magnet reads healthy before anything moves.
2. `control`, tap **D**. Note which way the cart physically goes; that direction
   is +x. Backwards? Set `CART_INVERT 1` and reflash.
3. `home`, then drive the cart a known distance and compare the reported `x`
   against a ruler. Disagreement means your pulley or microstep constants are
   wrong — fix the constants, don't invent a scale factor.
4. **Measure L_eff.** Let the pole hang, give it a small push, time 10 swings.
   `L_eff = g·(T/2π)²`. Then `set leff <value>`. Every balance gain is derived
   from this one number, so measuring beats guessing.
5. Tilt the pole toward +x and check in `data` that theta goes **positive**.
   If not, `ENC_INVERT 1` and reflash.
6. Send `fast`. Everything up to here was on the crawl profile; balancing
   needs real acceleration. Then hold the pole upright and send `bal`. It should fight you. Tune live, no
   reflashing: `set pw 9` for a stiffer pendulum loop, `set pc1 -2` if the cart
   wanders into the rail, `set bw 12` if it buzzes.
7. `auto`.

## 5. When it misbehaves

**Lost steps look exactly like bad tuning.** After any crash, check whether the
reported `x = 0` is still the physical centre of the rail. If it drifted, you're
losing steps: lower `amax_s`/`vmax`, raise Vref, or raise the motor supply
voltage as appropriate for the driver and motor. The current 60T swing-up
default of 0.8 m/s corresponds to 400 RPM; the motor supply is 24V.

**Rotor inertia also matters.** For example, 87 g·cm² through the 60T pulley's
19.10 mm pitch radius reflects to about 0.024 kg of apparent cart mass. This
is an illustration; the actual motor and pulley inertia have not been measured.

**Swing-up stalls at a fixed amplitude** → check `v` in the dashboard before
touching gains. The energy pump does work at a rate proportional to the cart's
*acceleration*, so the instant velocity saturates at `vmax`, acceleration goes
to zero and pumping stops for the rest of that half-swing. A flat-topped `v`
trace means you're speed-limited and no gain will fix it.

**Swing-up never gets going at all** → raise `amax_s`, or lower `kpx`; the
centring term steals energy from the pump. **Flies past upright too fast to catch** →
lower `ke` so the pump eases off near the top, or widen `catch_r`.

## Interactive pendulum simulator

Open [Pendulum Lab](simulator175/index.html) in a browser to test acceleration, jerk, speed ceilings, and four stepper input styles against the current measured 125 mm pendulum model, with the archived 175 mm presets retained. Includes calibration overlays, recorded command-waveform replay, comparisons, parameter sweeps, and CSV/JSON exports.

See [simulator documentation](simulator175/README.md) for local serving, model assumptions, source provenance, and validation. Run `node simulator175/test.js` to check the model and firmware-equation parity.

## Manual upright tuning (v17)

Use **`bal` / START upright** after manually raising the pendulum. The new upright-only session accepts a stopped start near upright, aborts beyond **±50° from calibrated upright**, brakes, returns to center and disables. It never switches to swing-up or automatically restarts. Rail protection also ends the trial. Existing motion limits remain **0.8 / 12 / 12 / 60** (speed / swing acceleration / balance acceleration / jerk).

The controller is four-state feedback, not PID. `bal_pw=8` is the simulation-screened first candidate; `set bal_pw 7` restores the old angular response for comparison while stopped. See [upright tuning and hardware procedure](analysis/upright_tuning.md). Compile/upload v17 and restart the Python console before testing; no physical trial has been performed.

## v19 direction trial

After seven v18 upright trials aborted on predictive rail protection and the user observed motion away from the falling side, **v19 sets `CART_INVERT=0` (previously 1)**. `ENC_INVERT=0`, upright raw 3416, `bal_pw=8`, motion limits .8/12/12/60 and ±50° upright abort/centering are retained. `params` now reports `cart_invert` so logs identify the physical direction mapping. The driver writes DIR on the first command as well as reversals; otherwise a first positive command could retain the boot LOW pin level after this polarity change.

Place the cart at physical center before reset/upload; after upload confirm firmware v19 and `cart_invert=0`, then use `data` and **START upright** / `bal` for a near-vertical release. Expected corrective cart motion is toward the falling side. The separate possible 2.9° reference discrepancy is not applied in this trial. [Physical review](analysis/upright_review_20260916/review.md).

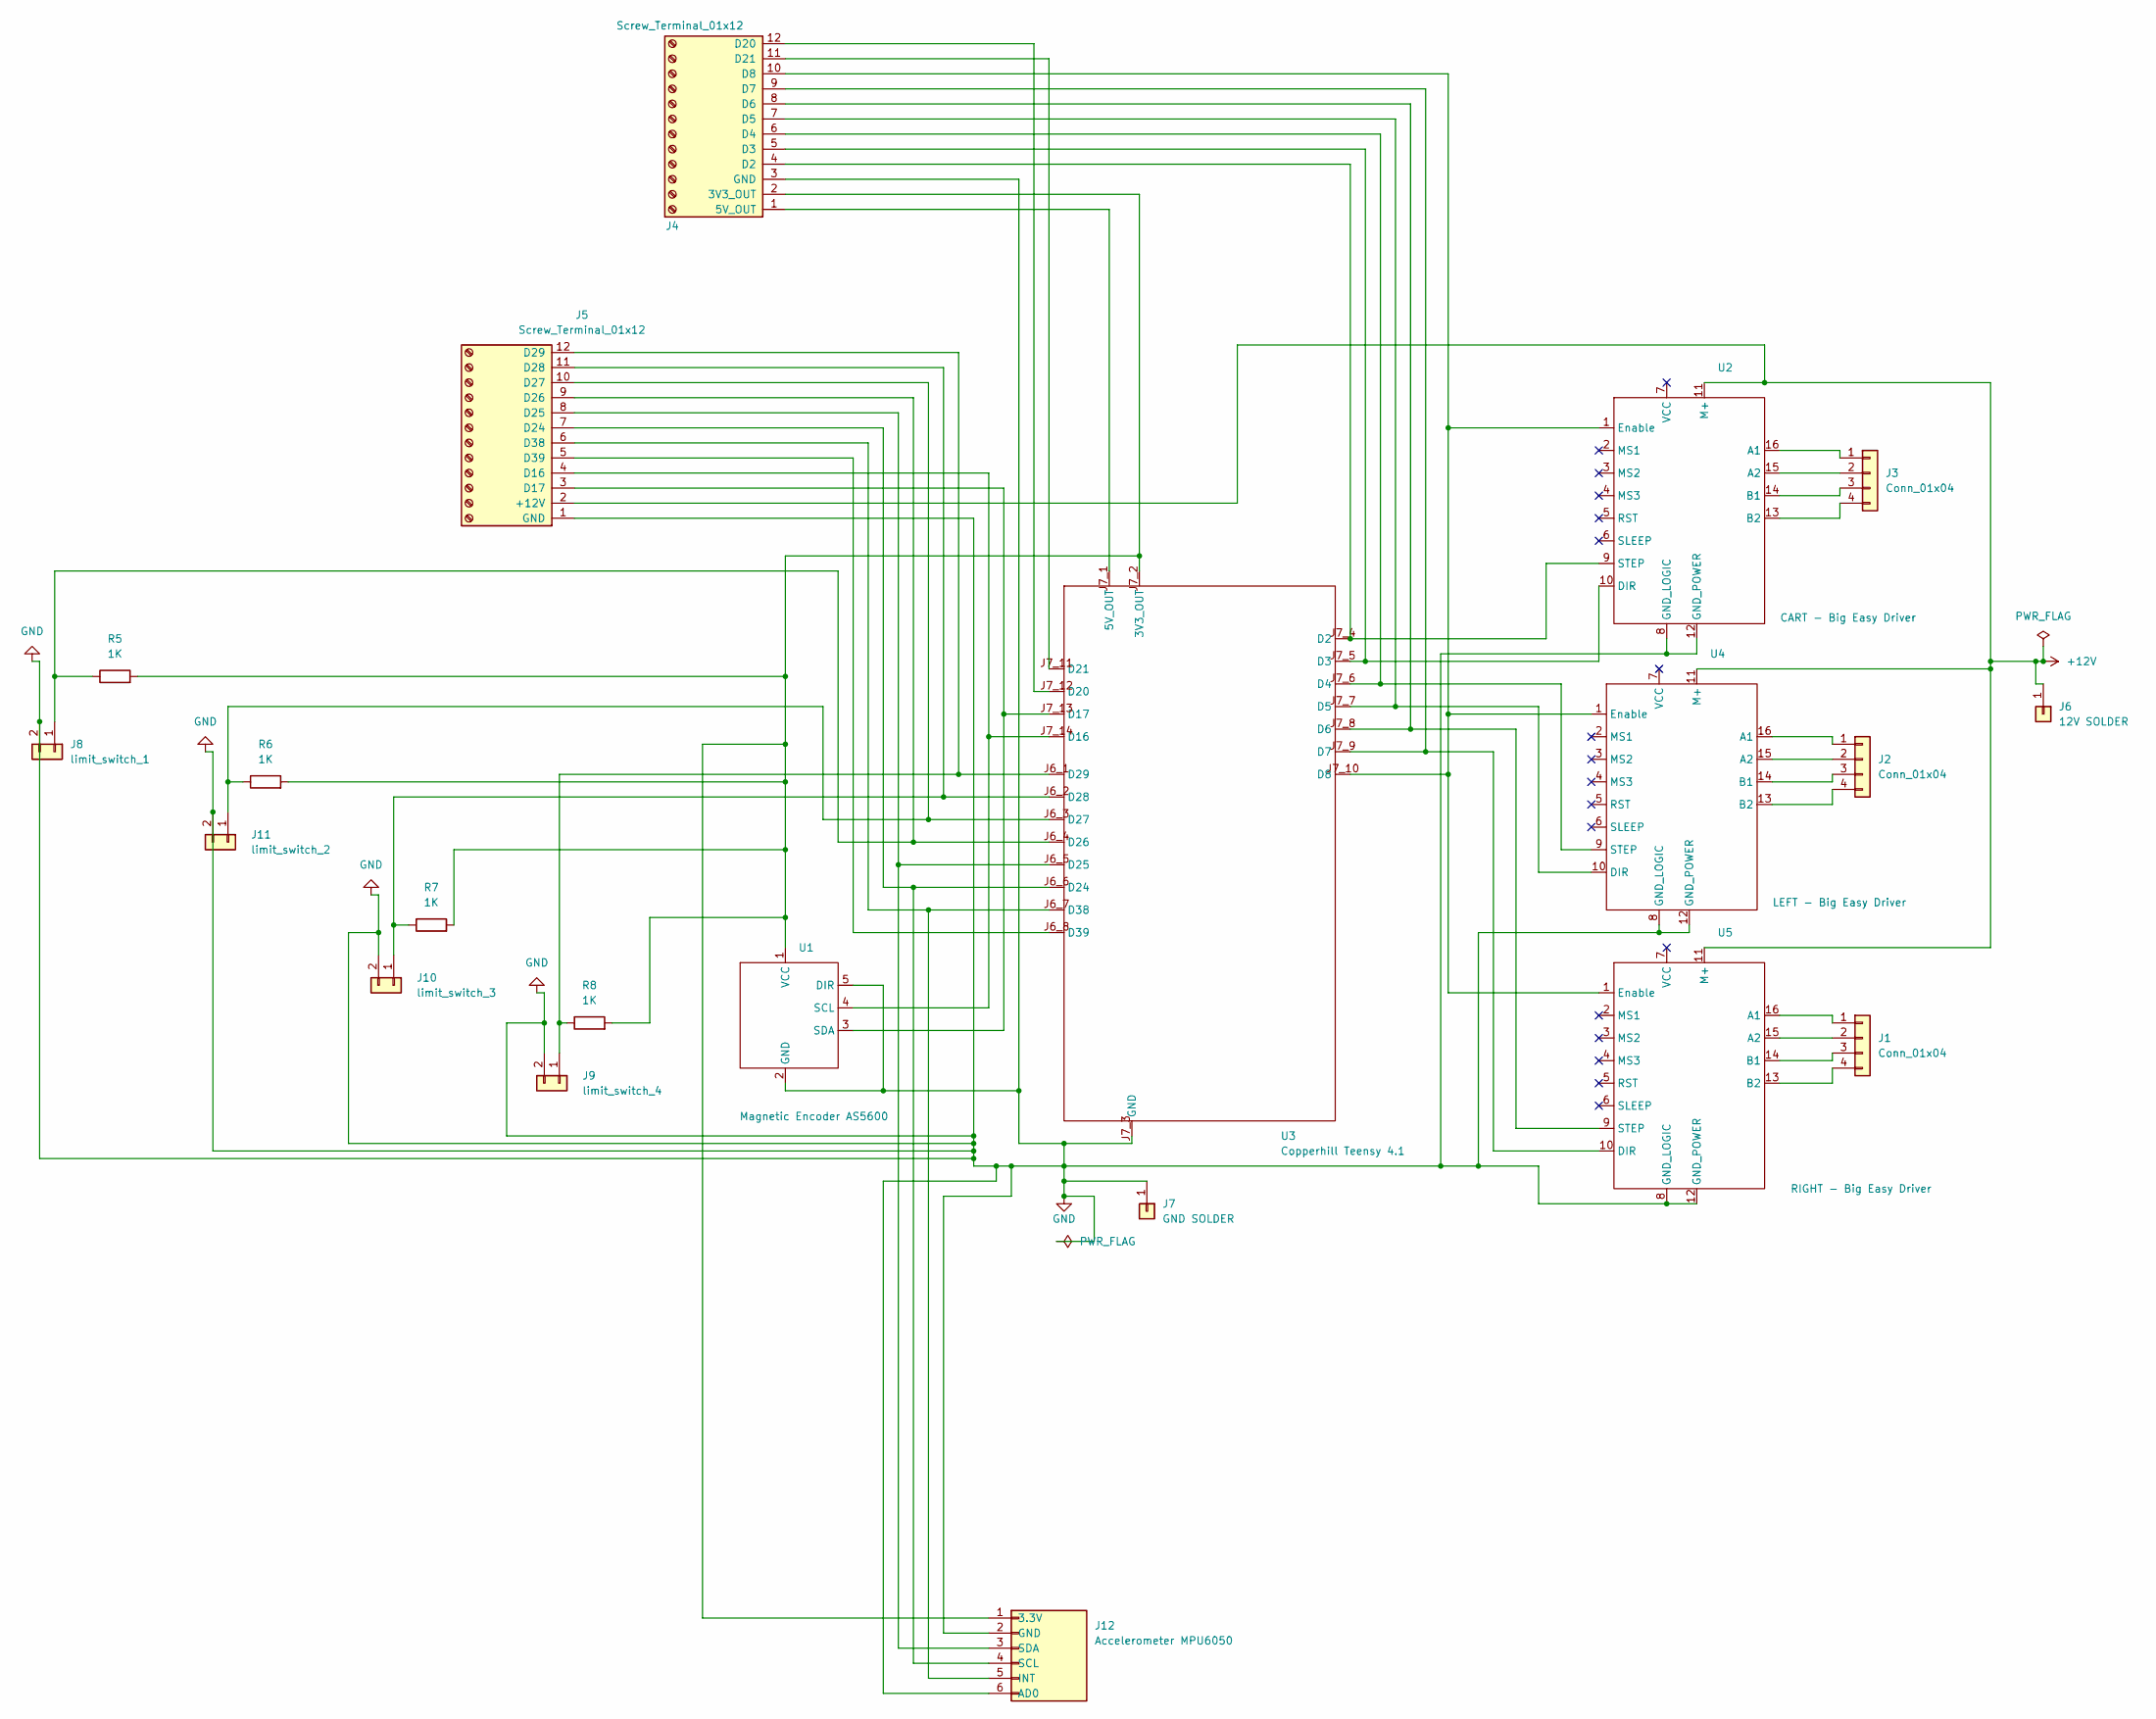
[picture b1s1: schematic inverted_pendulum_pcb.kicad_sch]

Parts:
J1, J2, J3: Conn_01x04; ScrewTerminal_1x04_P3.5mm_Horizontal
J4, J5: Screw_Terminal_01x12; 1x12_Screw_terminal
J6: 12V SOLDER; long_pad
J7: GND SOLDER; long_pad
J8: limit_switch_1; Limit_Switch_Wires_1x02_P2.54mm
J9: limit_switch_4; Limit_Switch_Wires_1x02_P2.54mm
J10: limit_switch_3; Limit_Switch_Wires_1x02_P2.54mm
J11: limit_switch_2; Limit_Switch_Wires_1x02_P2.54mm
J12: Accelerometer MPU6050; 1x06_P2.54mm
R5, R6, R7, R8: 1K; R_Axial_DIN0207_L6.3mm_D2.5mm_P7.62mm_Horizontal
U1: Magnetic Encoder AS5600; mag encoder
U2: CART - Big Easy Driver; BigEasyDriverPT2
U3: Copperhill Teensy 4.1; Teensy4.1
U4: LEFT - Big Easy Driver; BigEasyDriverPT2
U5: RIGHT - Big Easy Driver; BigEasyDriverPT2

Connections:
+12V: J5.2 (+12V), J6.1 (Pin_1_1), U2.11 (M+), U4.11 (M+), U5.11 (M+)
GND: J4.3 (GND), J5.1 (GND), J7.1 (Pin_1_1), J8.2, J9.2, J10.2, J11.2, J12.2 (GND), J12.6 (AD0), U1.2 (GND), U1.5 (DIR), U2.8 (GND_LOGIC), U2.12 (GND_POWER), U3.J7_3 (GND), U4.8 (GND_LOGIC), U4.12 (GND_POWER), U5.8 (GND_LOGIC), U5.12 (GND_POWER)
unnamed: J1.1, U5.16 (A1)
unnamed: J1.2, U5.15 (A2)
unnamed: J1.3, U5.14 (B1)
unnamed: J1.4, U5.13 (B2)
unnamed: J2.1, U4.16 (A1)
unnamed: J2.2, U4.15 (A2)
unnamed: J2.3, U4.14 (B1)
unnamed: J2.4, U4.13 (B2)
unnamed: J3.1, U2.16 (A1)
unnamed: J3.2, U2.15 (A2)
unnamed: J3.3, U2.14 (B1)
unnamed: J3.4, U2.13 (B2)
unnamed: J4.1 (5V_OUT), U3.J7_1 (5V_OUT)
unnamed: J4.4 (D2), U2.9 (STEP), U3.J7_4 (D2)
unnamed: J4.5 (D3), U2.10 (DIR), U3.J7_5 (D3)
unnamed: J4.6 (D4), U3.J7_6 (D4), U4.9 (STEP)
unnamed: J4.7 (D5), U3.J7_7 (D5), U4.10 (DIR)
unnamed: J4.8 (D6), U3.J7_8 (D6), U5.9 (STEP)
unnamed: J4.9 (D7), U3.J7_9 (D7), U5.10 (DIR)
unnamed: J4.10 (D8), U2.1 (Enable), U3.J7_10 (D8), U4.1 (Enable), U5.1 (Enable)
unnamed: J4.12 (D20), U3.J7_12 (D20)
unnamed: J4.11 (D21), U3.J7_11 (D21)
unnamed: J5.4 (D16), U1.4 (SCL), U3.J7_14 (D16)
unnamed: J5.3 (D17), U1.3 (SDA), U3.J7_13 (D17)
unnamed: J5.9 (D26), J8.1, R5.1, U3.J6_4 (D26)
unnamed: J5.12 (D29), J9.1, R8.1, U3.J6_1 (D29)
unnamed: J5.5 (D39), U3.J6_8 (D39)
unnamed: J5.11 (D28), J10.1, R7.1, U3.J6_2 (D28)
unnamed: J5.10 (D27), J11.1, R6.1, U3.J6_3 (D27)
unnamed: J4.2 (3V3_OUT), J12.1 (3.3V), R5.2, R6.2, R7.2, R8.2, U1.1 (VCC), U3.J7_2 (3V3_OUT)
unnamed: J5.6 (D38), J12.5 (INT), U3.J6_7 (D38)
unnamed: J5.7 (D24), J12.4 (SCL), U3.J6_6 (D24)
unnamed: J5.8 (D25), J12.3 (SDA), U3.J6_5 (D25)

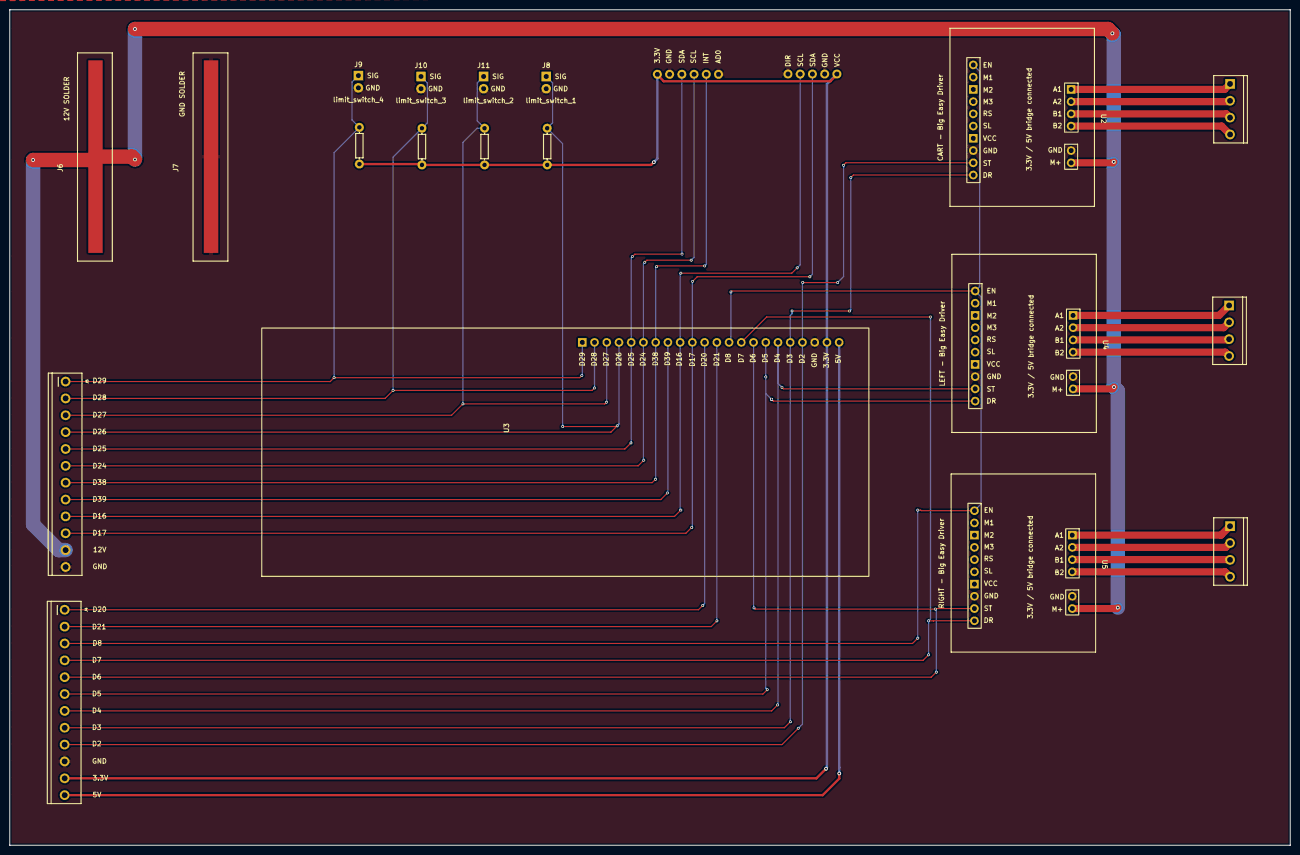
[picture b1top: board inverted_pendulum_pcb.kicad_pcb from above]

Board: 2 copper layers, 265.9 x 173.5 mm, 21 parts (0 on the bottom side), 35 nets.
